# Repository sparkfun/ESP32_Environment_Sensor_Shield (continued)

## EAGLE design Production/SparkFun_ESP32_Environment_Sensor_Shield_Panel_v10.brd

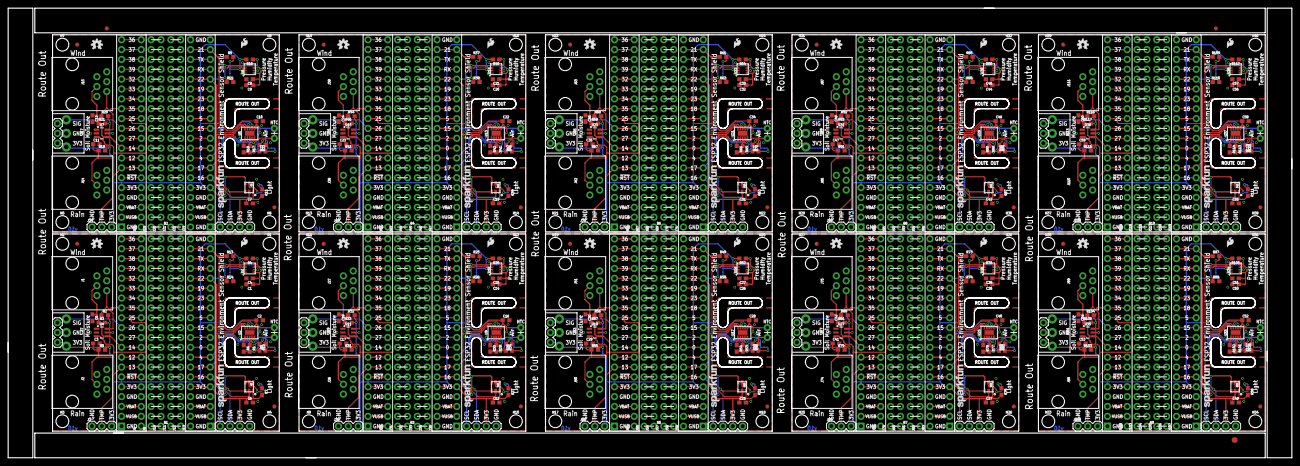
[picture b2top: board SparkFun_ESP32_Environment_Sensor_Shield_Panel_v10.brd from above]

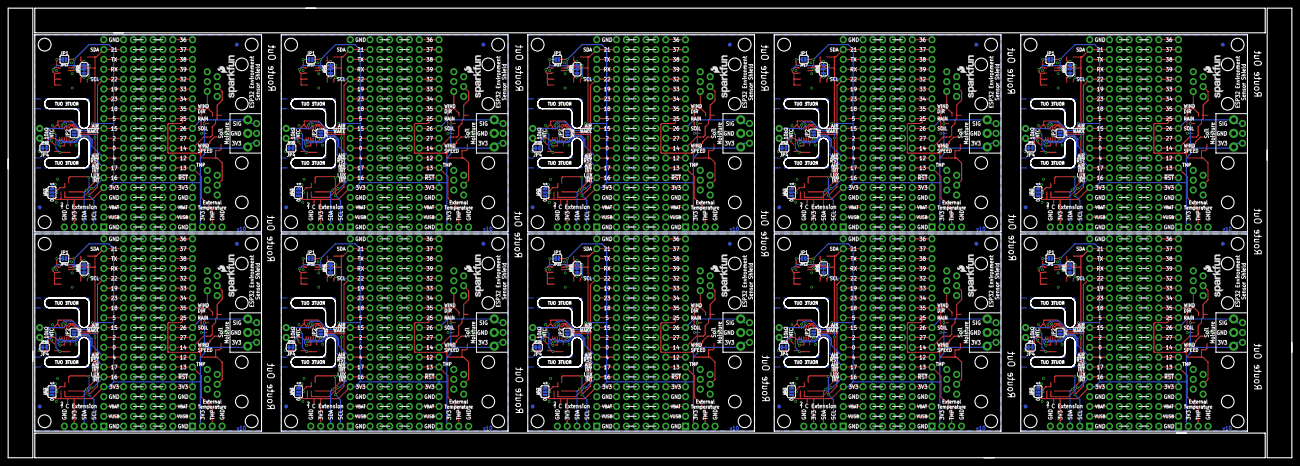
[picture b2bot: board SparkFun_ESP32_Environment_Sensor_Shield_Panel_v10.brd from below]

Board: 2 copper layers, 330.7 x 115.8 mm, 523 parts (80 on the bottom side), 840 nets.

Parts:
B1, B2, B3, B4, B5, B6, B7, B8, B9, B10: ESP32_THING_WO_ANT_KEEPOUT; ESP32_THING_NO_ANT
C1, C4, C6, C7, C8, C9, C13, C14, C15, C19, C20, C21, C25, C26, C27, C31, C32, C33, C37, C38, C39, C43, C44, C45, C49, C50, C51, C55, C56, C57: 0.1uF; 0603
C2, C3, C5, C10, C11, C12, C16, C17, C18, C22, C23, C24, C28, C29, C30, C34, C35, C36, C40, C41, C42, C46, C47, C48, C52, C53, C54, C58, C59, C60: 1.0uF; 0603
E$1: FIDUCIAL-1.5X3
E$7, E$8: FIDUCIAL-1X2
FD1, FD2, FD3, FD4, FD5, FD6, FD7, FD8, FD9, FD10, FD11, FD12, FD13, FD14, FD15, FD16, FD17, FD18, FD19, FD20, FD21, FD22, FD23, FD24, FD25, FD26, FD27, FD28, FD29, FD30, FD31, FD32, FD33, FD34, FD35, FD36, FD37, FD38, FD39, FD40: FIDUCIAL1X2; FIDUCIAL-1X2
H1, H2, H3, H4, H5, H6, H7, H8, H9, H10, H11, H12, H13, H14, H15, H16, H17, H18, H19, H20, H21, H22, H23, H24, H25, H26, H27, H28, H29, H30, H31, H32, H33, H34, H35, H36, H37, H38, H39, H40: STAND-OFF
J1, J15, J27, J39, J51, J63, J75, J87, J99, J111: WEATHER_METER-WIND; RJ11-6
J2, J14, J26, J38, J50, J62, J74, J86, J98, J110: WEATHER_METER-RAIN; RJ11-6
J3, J5, J16, J24, J28, J36, J40, J48, J52, J60, J64, J72, J76, J84, J88, J96, J100, J108, J112, J120: 1X03
J4, J9, J10, J11, J12, J13, J18, J19, J20, J21, J22, J23, J30, J31, J32, J33, J34, J35, J42, J43, J44, J45, J46, J47, J54, J55, J56, J57, J58, J59, J66, J67, J68, J69, J70, J71, J78, J79, J80, J81, J82, J83, J90, J91, J92, J93, J94, J95, J102, J103, J104, J105, J106, J107, J114, J115, J116, J117, J118, J119: 1X20_NOSILK
J6, J8, J25, J37, J49, J61, J73, J85, J97, J109: 1X04
J7, J17, J29, J41, J53, J65, J77, J89, J101, J113: SCREWTERMINAL-3.5MM-3-NS
JP1, JP2, JP7, JP8, JP12, JP13, JP17, JP18, JP22, JP23, JP27, JP28, JP32, JP33, JP37, JP38, JP42, JP43, JP47, JP48: SMT-JUMPER_2_NO_SILK
JP3, JP6, JP11, JP16, JP21, JP26, JP31, JP36, JP41, JP46: SMT-JUMPER_3_NO_SILK
JP4, JP9, JP14, JP19, JP24, JP29, JP34, JP39, JP44, JP49: SMT-JUMPER_2_NC_TRACE_SILK
JP5, JP10, JP15, JP20, JP25, JP30, JP35, JP40, JP45, JP50: SMT-JUMPER_3_2-NC_TRACE_SILK
LOGO1, LOGO5, LOGO9, LOGO13, LOGO17, LOGO21, LOGO25, LOGO29, LOGO33, LOGO37: SFE_LOGO_NAME.1_INCH; SFE_LOGO_NAME_.1
LOGO2, LOGO7, LOGO11, LOGO15, LOGO19, LOGO23, LOGO27, LOGO31, LOGO35, LOGO39: SFE_LOGO_NAME_FLAME.1_INCH; SFE_LOGO_NAME_FLAME_.1
LOGO3, LOGO8, LOGO12, LOGO16, LOGO20, LOGO24, LOGO28, LOGO32, LOGO36, LOGO40: SFE_LOGO_FLAME.1_INCH; SFE_LOGO_FLAME_.1
LOGO4, LOGO6, LOGO10, LOGO14, LOGO18, LOGO22, LOGO26, LOGO30, LOGO34, LOGO38: OSHW-LOGOS; OSHW-LOGO-S
R1, R4, R6, R7, R15, R16, R17, R18, R27, R28, R29, R30, R39, R40, R41, R42, R51, R52, R53, R54, R63, R64, R65, R66, R75, R76, R77, R78, R87, R88, R89, R90, R99, R100, R101, R102, R111, R112, R113, R114: 100k; 0603
R2, R8, R10, R20, R22, R23, R32, R34, R35, R44, R46, R47, R56, R58, R59, R68, R70, R71, R80, R82, R83, R92, R94, R95, R104, R106, R107, R116, R118, R119: 10k; 0603
R3, R9, R19, R21, R31, R33, R43, R45, R55, R57, R67, R69, R79, R81, R91, R93, R103, R105, R115, R117: 1k; 0603
R5, R11, R13, R14, R25, R26, R37, R38, R49, R50, R61, R62, R73, R74, R85, R86, R97, R98, R109, R110: 4.7k; 0603
R12, R24, R36, R48, R60, R72, R84, R96, R108, R120: DNP; AXIAL-0.1
U1, U6, U10, U14, U18, U22, U26, U30, U34, U38: BME280; LGA-8-2.5X2.5
U2, U5, U9, U13, U17, U21, U25, U29, U33, U37: CCS811; LGA10-2.7X4.0MM
U3, U8, U12, U16, U20, U24, U28, U32, U36, U40: APDS-9301; CHIPLED-6
U4, U7, U11, U15, U19, U23, U27, U31, U35, U39: TVS Diode; SOT-23-6

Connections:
3.3V: B1.5, B1.36, C1.1, C2.1, C4.1, C6.1, J3.3, J4.5, J5.1, J7.3, J8.2, J13.5, JP5.2, R1.2, R2.2, R3.2, R4.2, R6.2, R7.2, R9.2, R10.2, U1.2, U1.6, U1.8, U2.6, U3.P1, U4.5
3.3V1: B2.5, B2.36, C7.1, C8.1, C9.1, C10.1, J6.2, J16.1, J17.3, J18.5, J23.5, J24.3, JP10.2, R15.2, R16.2, R17.2, R18.2, R19.2, R20.2, R21.2, R22.2, U5.6, U6.2, U6.6, U6.8, U7.5, U8.P1
3.3V2: B3.5, B3.36, C13.1, C14.1, C15.1, C16.1, J25.2, J28.1, J29.3, J30.5, J35.5, J36.3, JP15.2, R27.2, R28.2, R29.2, R30.2, R31.2, R32.2, R33.2, R34.2, U9.6, U10.2, U10.6, U10.8, U11.5, U12.P1
3.3V3: B4.5, B4.36, C19.1, C20.1, C21.1, C22.1, J37.2, J40.1, J41.3, J42.5, J47.5, J48.3, JP20.2, R39.2, R40.2, R41.2, R42.2, R43.2, R44.2, R45.2, R46.2, U13.6, U14.2, U14.6, U14.8, U15.5, U16.P1
3.3V4: B5.5, B5.36, C25.1, C26.1, C27.1, C28.1, J49.2, J52.1, J53.3, J54.5, J59.5, J60.3, JP25.2, R51.2, R52.2, R53.2, R54.2, R55.2, R56.2, R57.2, R58.2, U17.6, U18.2, U18.6, U18.8, U19.5, U20.P1
3.3V5: B6.5, B6.36, C31.1, C32.1, C33.1, C34.1, J61.2, J64.1, J65.3, J66.5, J71.5, J72.3, JP30.2, R63.2, R64.2, R65.2, R66.2, R67.2, R68.2, R69.2, R70.2, U21.6, U22.2, U22.6, U22.8, U23.5, U24.P1
3.3V6: B7.5, B7.36, C37.1, C38.1, C39.1, C40.1, J73.2, J76.1, J77.3, J78.5, J83.5, J84.3, JP35.2, R75.2, R76.2, R77.2, R78.2, R79.2, R80.2, R81.2, R82.2, U25.6, U26.2, U26.6, U26.8, U27.5, U28.P1
3.3V7: B8.5, B8.36, C43.1, C44.1, C45.1, C46.1, J85.2, J88.1, J89.3, J90.5, J95.5, J96.3, JP40.2, R87.2, R88.2, R89.2, R90.2, R91.2, R92.2, R93.2, R94.2, U29.6, U30.2, U30.6, U30.8, U31.5, U32.P1
3.3V8: B9.5, B9.36, C49.1, C50.1, C51.1, C52.1, J97.2, J100.1, J101.3, J102.5, J107.5, J108.3, JP45.2, R99.2, R100.2, R101.2, R102.2, R103.2, R104.2, R105.2, R106.2, U33.6, U34.2, U34.6, U34.8, U35.5, U36.P1
3.3V9: B10.5, B10.36, C55.1, C56.1, C57.1, C58.1, J109.2, J112.1, J113.3, J114.5, J119.5, J120.3, JP50.2, R111.2, R112.2, R113.2, R114.2, R115.2, R116.2, R117.2, R118.2, U37.6, U38.2, U38.6, U38.8, U39.5, U40.P1
ADDR_TSL1: JP6.2, U8.P3
ADDR_TSL2: JP11.2, U12.P3
ADDR_TSL3: JP16.2, U16.P3
ADDR_TSL4: JP21.2, U20.P3
ADDR_TSL5: JP26.2, U24.P3
ADDR_TSL6: JP31.2, U28.P3
ADDR_TSL7: JP36.2, U32.P3
ADDR_TSL8: JP41.2, U36.P3
ADDR_TSL9: JP46.2, U40.P3
ADDR_TSL2561: JP3.2, U3.P3
CCS811_!INT!: B1.34, J13.7, U2.3
CCS811_!INT!1: B2.34, J23.7, U5.3
CCS811_!INT!2: B3.34, J35.7, U9.3
CCS811_!INT!3: B4.34, J47.7, U13.3
CCS811_!INT!4: B5.34, J59.7, U17.3
CCS811_!INT!5: B6.34, J71.7, U21.3
CCS811_!INT!6: B7.34, J83.7, U25.3
CCS811_!INT!7: B8.34, J95.7, U29.3
CCS811_!INT!8: B9.34, J107.7, U33.3
CCS811_!INT!9: B10.34, J119.7, U37.3
CCS811_!RST!: B1.33, J13.8, R1.1, U2.2
CCS811_!RST!1: B2.33, J23.8, R17.1, U5.2
CCS811_!RST!2: B3.33, J35.8, R29.1, U9.2
CCS811_!RST!3: B4.33, J47.8, R41.1, U13.2
CCS811_!RST!4: B5.33, J59.8, R53.1, U17.2
CCS811_!RST!5: B6.33, J71.8, R65.1, U21.2
CCS811_!RST!6: B7.33, J83.8, R77.1, U25.2
CCS811_!RST!7: B8.33, J95.8, R89.1, U29.2
CCS811_!RST!8: B9.33, J107.8, R101.1, U33.2
CCS811_!RST!9: B10.33, J119.8, R113.1, U37.2
CCS811_!WAKE!: B1.30, J13.11, U2.7
CCS811_!WAKE!1: B2.30, J23.11, U5.7
CCS811_!WAKE!2: B3.30, J35.11, U9.7
CCS811_!WAKE!3: B4.30, J47.11, U13.7
CCS811_!WAKE!4: B5.30, J59.11, U17.7
CCS811_!WAKE!5: B6.30, J71.11, U21.7
CCS811_!WAKE!6: B7.30, J83.11, U25.7
CCS811_!WAKE!7: B8.30, J95.11, U29.7
CCS811_!WAKE!8: B9.30, J107.11, U33.7
CCS811_!WAKE!9: B10.30, J119.11, U37.7
CCS811_ADDR: JP2.2, R6.1, U2.1
CCS811_ADDR1: JP8.2, R18.1, U5.1
CCS811_ADDR2: JP13.2, R30.1, U9.1
CCS811_ADDR3: JP18.2, R42.1, U13.1
CCS811_ADDR4: JP23.2, R54.1, U17.1
CCS811_ADDR5: JP28.2, R66.1, U21.1
CCS811_ADDR6: JP33.2, R78.1, U25.1
CCS811_ADDR7: JP38.2, R90.1, U29.1
CCS811_ADDR8: JP43.2, R102.1, U33.1
CCS811_ADDR9: JP48.2, R114.1, U37.1
CCS811_AUX: JP4.2, R10.1, R12.P$1, U2.8
CCS811_AUX1: JP9.2, R22.1, R24.P$1, U5.8
CCS811_AUX2: JP14.2, R34.1, R36.P$1, U9.8
CCS811_AUX3: JP19.2, R46.1, R48.P$1, U13.8
CCS811_AUX4: JP24.2, R58.1, R60.P$1, U17.8
CCS811_AUX5: JP29.2, R70.1, R72.P$1, U21.8
CCS811_AUX6: JP34.2, R82.1, R84.P$1, U25.8
CCS811_AUX7: JP39.2, R94.1, R96.P$1, U29.8
CCS811_AUX8: JP44.2, R106.1, R108.P$1, U33.8
CCS811_AUX9: JP49.2, R118.1, R120.P$1, U37.8
EXT_TEMPERATURE: B1.7, J3.2, J4.7
EXT_TEMPERATURE1: B2.7, J18.7, J24.2
EXT_TEMPERATURE2: B3.7, J30.7, J36.2
EXT_TEMPERATURE3: B4.7, J42.7, J48.2
EXT_TEMPERATURE4: B5.7, J54.7, J60.2
EXT_TEMPERATURE5: B6.7, J66.7, J72.2
EXT_TEMPERATURE6: B7.7, J78.7, J84.2
EXT_TEMPERATURE7: B8.7, J90.7, J96.2
EXT_TEMPERATURE8: B9.7, J102.7, J108.2
EXT_TEMPERATURE9: B10.7, J114.7, J120.2
GND: B1.1, B1.4, B1.21, B1.37, B1.40, C1.2, C2.2, C3.2, C4.2, C5.2, C6.2, J1.2, J1.3, J2.3, J3.1, J4.1, J4.4, J5.2, J7.2, J8.1, J13.1, J13.4, J13.20, JP1.1, JP2.1, JP3.1, U1.1, U1.7, U2.EP, U3.P2, U4.2
GND1: B2.1, B2.4, B2.21, B2.37, B2.40, C7.2, C8.2, C9.2, C10.2, C11.2, C12.2, J6.1, J14.3, J15.2, J15.3, J16.2, J17.2, J18.1, J18.4, J23.1, J23.4, J23.20, J24.1, JP6.1, JP7.1, JP8.1, U5.EP, U6.1, U6.7, U7.2, U8.P2
GND2: B3.1, B3.4, B3.21, B3.37, B3.40, C13.2, C14.2, C15.2, C16.2, C17.2, C18.2, J25.1, J26.3, J27.2, J27.3, J28.2, J29.2, J30.1, J30.4, J35.1, J35.4, J35.20, J36.1, JP11.1, JP12.1, JP13.1, U9.EP, U10.1, U10.7, U11.2, U12.P2
GND3: B4.1, B4.4, B4.21, B4.37, B4.40, C19.2, C20.2, C21.2, C22.2, C23.2, C24.2, J37.1, J38.3, J39.2, J39.3, J40.2, J41.2, J42.1, J42.4, J47.1, J47.4, J47.20, J48.1, JP16.1, JP17.1, JP18.1, U13.EP, U14.1, U14.7, U15.2, U16.P2
GND4: B5.1, B5.4, B5.21, B5.37, B5.40, C25.2, C26.2, C27.2, C28.2, C29.2, C30.2, J49.1, J50.3, J51.2, J51.3, J52.2, J53.2, J54.1, J54.4, J59.1, J59.4, J59.20, J60.1, JP21.1, JP22.1, JP23.1, U17.EP, U18.1, U18.7, U19.2, U20.P2
GND5: B6.1, B6.4, B6.21, B6.37, B6.40, C31.2, C32.2, C33.2, C34.2, C35.2, C36.2, J61.1, J62.3, J63.2, J63.3, J64.2, J65.2, J66.1, J66.4, J71.1, J71.4, J71.20, J72.1, JP26.1, JP27.1, JP28.1, U21.EP, U22.1, U22.7, U23.2, U24.P2
GND6: B7.1, B7.4, B7.21, B7.37, B7.40, C37.2, C38.2, C39.2, C40.2, C41.2, C42.2, J73.1, J74.3, J75.2, J75.3, J76.2, J77.2, J78.1, J78.4, J83.1, J83.4, J83.20, J84.1, JP31.1, JP32.1, JP33.1, U25.EP, U26.1, U26.7, U27.2, U28.P2
GND7: B8.1, B8.4, B8.21, B8.37, B8.40, C43.2, C44.2, C45.2, C46.2, C47.2, C48.2, J85.1, J86.3, J87.2, J87.3, J88.2, J89.2, J90.1, J90.4, J95.1, J95.4, J95.20, J96.1, JP36.1, JP37.1, JP38.1, U29.EP, U30.1, U30.7, U31.2, U32.P2
GND8: B9.1, B9.4, B9.21, B9.37, B9.40, C49.2, C50.2, C51.2, C52.2, C53.2, C54.2, J97.1, J98.3, J99.2, J99.3, J100.2, J101.2, J102.1, J102.4, J107.1, J107.4, J107.20, J108.1, JP41.1, JP42.1, JP43.1, U33.EP, U34.1, U34.7, U35.2, U36.P2
GND9: B10.1, B10.4, B10.21, B10.37, B10.40, C55.2, C56.2, C57.2, C58.2, C59.2, C60.2, J109.1, J110.3, J111.2, J111.3, J112.2, J113.2, J114.1, J114.4, J119.1, J119.4, J119.20, J120.1, JP46.1, JP47.1, JP48.1, U37.EP, U38.1, U38.7, U39.2, U40.P2
LUX_INT: B1.35, J13.6, U3.P6
LUX_INT1: B2.35, J23.6, U8.P6
LUX_INT2: B3.35, J35.6, U12.P6
LUX_INT3: B4.35, J47.6, U16.P6
LUX_INT4: B5.35, J59.6, U20.P6
LUX_INT5: B6.35, J71.6, U24.P6
LUX_INT6: B7.35, J83.6, U28.P6
LUX_INT7: B8.35, J95.6, U32.P6
LUX_INT8: B9.35, J107.6, U36.P6
LUX_INT9: B10.35, J119.6, U40.P6
unnamed: JP3.3, R7.1
unnamed: JP1.2, R4.1, U1.5
unnamed: JP4.1, R8.1
unnamed: JP5.3, R13.2
unnamed: JP5.1, R14.2
unnamed: B1.2, J4.2
unnamed: B1.3, J4.3
unnamed: B1.6, J4.6
unnamed: B1.10, J4.10
unnamed: JP6.3, R15.1
unnamed: B1.14, J4.14
unnamed: B1.15, J4.15
unnamed: B1.16, J4.16
unnamed: B1.17, J4.17
unnamed: B1.18, J4.18
unnamed: B1.19, J4.19
unnamed: B1.20, J4.20
unnamed: B1.39, J13.2
unnamed: B1.38, J13.3
unnamed: B1.32, J13.9
unnamed: B1.31, J13.10
unnamed: B1.8, J4.8
unnamed: B1.29, J13.12
unnamed: B1.28, J13.13
unnamed: B1.27, J13.14
unnamed: B1.26, J13.15
unnamed: B1.24, J13.17
unnamed: B1.23, J13.18
unnamed: J11.1, J12.1
unnamed: J11.2, J12.2
unnamed: J11.3, J12.3
unnamed: J11.4, J12.4
unnamed: J11.5, J12.5
unnamed: J11.6, J12.6
unnamed: J11.7, J12.7
unnamed: J11.8, J12.8
unnamed: J11.9, J12.9
unnamed: J11.10, J12.10
unnamed: J11.11, J12.11
unnamed: J11.12, J12.12
unnamed: J11.13, J12.13
unnamed: J11.14, J12.14
unnamed: J11.15, J12.15
unnamed: J11.16, J12.16
unnamed: J11.17, J12.17
unnamed: J11.18, J12.18
unnamed: J11.19, J12.19
unnamed: J11.20, J12.20
unnamed: J9.1, J10.1
unnamed: J9.2, J10.2
unnamed: J9.3, J10.3
unnamed: J9.4, J10.4
unnamed: J9.5, J10.5
unnamed: J9.6, J10.6
unnamed: J9.7, J10.7
unnamed: J9.8, J10.8
unnamed: J9.9, J10.9
unnamed: J9.10, J10.10
unnamed: J9.11, J10.11
unnamed: J9.12, J10.12
unnamed: J9.13, J10.13
unnamed: J9.14, J10.14
unnamed: J9.15, J10.15
unnamed: J9.16, J10.16
unnamed: J9.17, J10.17
unnamed: J9.18, J10.18
unnamed: J9.19, J10.19
unnamed: J9.20, J10.20
unnamed: JP7.2, R16.1, U6.5
unnamed: JP9.1, R23.1
unnamed: JP10.3, R5.2
unnamed: JP10.1, R11.2
unnamed: B2.2, J18.2
unnamed: B2.3, J18.3
unnamed: B2.6, J18.6
unnamed: B2.14, J18.14
unnamed: B2.15, J18.15
unnamed: B2.16, J18.16
unnamed: B2.17, J18.17
unnamed: B2.18, J18.18
unnamed: B2.19, J18.19
unnamed: B2.20, J18.20
unnamed: B2.39, J23.2
unnamed: B2.38, J23.3
unnamed: B2.32, J23.9
unnamed: B2.29, J23.12
unnamed: B2.28, J23.13
unnamed: B2.27, J23.14
unnamed: B2.26, J23.15
unnamed: B2.24, J23.17
unnamed: B2.23, J23.18
unnamed: J21.1, J22.1
unnamed: J21.2, J22.2
unnamed: J21.3, J22.3
unnamed: J21.4, J22.4
unnamed: J21.5, J22.5
unnamed: J21.6, J22.6
unnamed: J21.7, J22.7
unnamed: J21.8, J22.8
unnamed: J21.9, J22.9
unnamed: J21.10, J22.10
unnamed: J21.11, J22.11
unnamed: J21.12, J22.12
unnamed: J21.13, J22.13
unnamed: J21.14, J22.14
unnamed: J21.15, J22.15
unnamed: J21.16, J22.16
unnamed: J21.17, J22.17
unnamed: J21.18, J22.18
unnamed: J21.19, J22.19
unnamed: J21.20, J22.20
unnamed: J19.1, J20.1
unnamed: J19.2, J20.2
unnamed: J19.3, J20.3
unnamed: J19.4, J20.4
unnamed: J19.5, J20.5
unnamed: J19.6, J20.6
unnamed: J19.7, J20.7
unnamed: J19.8, J20.8
unnamed: J19.9, J20.9
unnamed: J19.10, J20.10
unnamed: J19.11, J20.11
unnamed: J19.12, J20.12
unnamed: J19.13, J20.13
unnamed: J19.14, J20.14
unnamed: J19.15, J20.15
unnamed: J19.16, J20.16
unnamed: J19.17, J20.17
unnamed: J19.18, J20.18
unnamed: J19.19, J20.19
unnamed: J19.20, J20.20
unnamed: B2.31, J23.10
unnamed: B2.8, J18.8
unnamed: B2.10, J18.10
unnamed: JP11.3, R27.1
unnamed: JP12.2, R28.1, U10.5
unnamed: JP14.1, R35.1
unnamed: JP15.3, R25.2
unnamed: JP15.1, R26.2
unnamed: B3.2, J30.2
unnamed: B3.3, J30.3
unnamed: B3.6, J30.6
unnamed: B3.14, J30.14
unnamed: B3.15, J30.15
unnamed: B3.16, J30.16
unnamed: B3.17, J30.17
unnamed: B3.18, J30.18
unnamed: B3.19, J30.19
unnamed: B3.20, J30.20
unnamed: B3.39, J35.2
unnamed: B3.38, J35.3
unnamed: B3.32, J35.9
unnamed: B3.29, J35.12
unnamed: B3.28, J35.13
unnamed: B3.27, J35.14
unnamed: B3.26, J35.15
unnamed: B3.24, J35.17
unnamed: B3.23, J35.18
unnamed: J33.1, J34.1
unnamed: J33.2, J34.2
unnamed: J33.3, J34.3
unnamed: J33.4, J34.4
unnamed: J33.5, J34.5
unnamed: J33.6, J34.6
unnamed: J33.7, J34.7
unnamed: J33.8, J34.8
unnamed: J33.9, J34.9
unnamed: J33.10, J34.10
unnamed: J33.11, J34.11
unnamed: J33.12, J34.12
unnamed: J33.13, J34.13
unnamed: J33.14, J34.14
unnamed: J33.15, J34.15
unnamed: J33.16, J34.16
unnamed: J33.17, J34.17
unnamed: J33.18, J34.18
unnamed: J33.19, J34.19
unnamed: J33.20, J34.20
unnamed: J31.1, J32.1
unnamed: J31.2, J32.2
unnamed: J31.3, J32.3
unnamed: J31.4, J32.4
unnamed: J31.5, J32.5
unnamed: J31.6, J32.6
unnamed: J31.7, J32.7
unnamed: J31.8, J32.8
unnamed: J31.9, J32.9
unnamed: J31.10, J32.10
unnamed: J31.11, J32.11
unnamed: J31.12, J32.12
unnamed: J31.13, J32.13
unnamed: J31.14, J32.14
unnamed: J31.15, J32.15
unnamed: J31.16, J32.16
unnamed: J31.17, J32.17
unnamed: J31.18, J32.18
unnamed: J31.19, J32.19
unnamed: J31.20, J32.20
unnamed: B3.31, J35.10
unnamed: B3.8, J30.8
unnamed: B3.10, J30.10
unnamed: JP16.3, R39.1
unnamed: JP17.2, R40.1, U14.5
unnamed: JP19.1, R47.1
unnamed: JP20.3, R37.2
unnamed: JP20.1, R38.2
unnamed: B4.2, J42.2
unnamed: B4.3, J42.3
unnamed: B4.6, J42.6
unnamed: B4.14, J42.14
unnamed: B4.15, J42.15
unnamed: B4.16, J42.16
unnamed: B4.17, J42.17
unnamed: B4.18, J42.18
unnamed: B4.19, J42.19
unnamed: B4.20, J42.20
unnamed: B4.39, J47.2
unnamed: B4.38, J47.3
unnamed: B4.32, J47.9
unnamed: B4.29, J47.12
unnamed: B4.28, J47.13
unnamed: B4.27, J47.14
unnamed: B4.26, J47.15
unnamed: B4.24, J47.17
unnamed: B4.23, J47.18
unnamed: J45.1, J46.1
unnamed: J45.2, J46.2
unnamed: J45.3, J46.3
unnamed: J45.4, J46.4
unnamed: J45.5, J46.5
unnamed: J45.6, J46.6
unnamed: J45.7, J46.7
unnamed: J45.8, J46.8
unnamed: J45.9, J46.9
unnamed: J45.10, J46.10
unnamed: J45.11, J46.11
unnamed: J45.12, J46.12
unnamed: J45.13, J46.13
unnamed: J45.14, J46.14
unnamed: J45.15, J46.15
unnamed: J45.16, J46.16
unnamed: J45.17, J46.17
unnamed: J45.18, J46.18
unnamed: J45.19, J46.19
unnamed: J45.20, J46.20
unnamed: J43.1, J44.1
unnamed: J43.2, J44.2
unnamed: J43.3, J44.3
unnamed: J43.4, J44.4
unnamed: J43.5, J44.5
unnamed: J43.6, J44.6
unnamed: J43.7, J44.7
unnamed: J43.8, J44.8
unnamed: J43.9, J44.9
unnamed: J43.10, J44.10
unnamed: J43.11, J44.11
unnamed: J43.12, J44.12
unnamed: J43.13, J44.13
unnamed: J43.14, J44.14
unnamed: J43.15, J44.15
unnamed: J43.16, J44.16
unnamed: J43.17, J44.17
unnamed: J43.18, J44.18
unnamed: J43.19, J44.19
unnamed: J43.20, J44.20
unnamed: B4.31, J47.10
unnamed: B4.8, J42.8
unnamed: B4.10, J42.10
unnamed: JP21.3, R51.1
unnamed: JP22.2, R52.1, U18.5
unnamed: JP24.1, R59.1
unnamed: JP25.3, R49.2
unnamed: JP25.1, R50.2
unnamed: B5.2, J54.2
unnamed: B5.3, J54.3
unnamed: B5.6, J54.6
unnamed: B5.14, J54.14
unnamed: B5.15, J54.15
unnamed: B5.16, J54.16
unnamed: B5.17, J54.17
unnamed: B5.18, J54.18
unnamed: B5.19, J54.19
unnamed: B5.20, J54.20
unnamed: B5.39, J59.2
unnamed: B5.38, J59.3
unnamed: B5.32, J59.9
unnamed: B5.29, J59.12
unnamed: B5.28, J59.13
unnamed: B5.27, J59.14
unnamed: B5.26, J59.15
unnamed: B5.24, J59.17
unnamed: B5.23, J59.18
unnamed: J57.1, J58.1
unnamed: J57.2, J58.2
unnamed: J57.3, J58.3
unnamed: J57.4, J58.4
unnamed: J57.5, J58.5
unnamed: J57.6, J58.6
unnamed: J57.7, J58.7
unnamed: J57.8, J58.8
unnamed: J57.9, J58.9
unnamed: J57.10, J58.10
unnamed: J57.11, J58.11
unnamed: J57.12, J58.12
unnamed: J57.13, J58.13
unnamed: J57.14, J58.14
unnamed: J57.15, J58.15
unnamed: J57.16, J58.16
unnamed: J57.17, J58.17
unnamed: J57.18, J58.18
unnamed: J57.19, J58.19
unnamed: J57.20, J58.20
unnamed: J55.1, J56.1
unnamed: J55.2, J56.2
unnamed: J55.3, J56.3
unnamed: J55.4, J56.4
unnamed: J55.5, J56.5
unnamed: J55.6, J56.6
unnamed: J55.7, J56.7
unnamed: J55.8, J56.8
unnamed: J55.9, J56.9
unnamed: J55.10, J56.10
unnamed: J55.11, J56.11
unnamed: J55.12, J56.12
unnamed: J55.13, J56.13
unnamed: J55.14, J56.14
unnamed: J55.15, J56.15
unnamed: J55.16, J56.16
unnamed: J55.17, J56.17
unnamed: J55.18, J56.18
unnamed: J55.19, J56.19
unnamed: J55.20, J56.20
unnamed: B5.31, J59.10
unnamed: B5.8, J54.8
unnamed: B5.10, J54.10
unnamed: JP26.3, R63.1
unnamed: JP27.2, R64.1, U22.5
unnamed: JP29.1, R71.1
unnamed: JP30.3, R61.2
unnamed: JP30.1, R62.2
unnamed: B6.2, J66.2
unnamed: B6.3, J66.3
unnamed: B6.6, J66.6
unnamed: B6.14, J66.14
unnamed: B6.15, J66.15
unnamed: B6.16, J66.16
unnamed: B6.17, J66.17
unnamed: B6.18, J66.18
unnamed: B6.19, J66.19
unnamed: B6.20, J66.20
unnamed: B6.39, J71.2
unnamed: B6.38, J71.3
unnamed: B6.32, J71.9
unnamed: B6.29, J71.12
unnamed: B6.28, J71.13
unnamed: B6.27, J71.14
unnamed: B6.26, J71.15
unnamed: B6.24, J71.17
unnamed: B6.23, J71.18
unnamed: J69.1, J70.1
unnamed: J69.2, J70.2
unnamed: J69.3, J70.3
unnamed: J69.4, J70.4
unnamed: J69.5, J70.5
unnamed: J69.6, J70.6
unnamed: J69.7, J70.7
unnamed: J69.8, J70.8
unnamed: J69.9, J70.9
unnamed: J69.10, J70.10
unnamed: J69.11, J70.11
unnamed: J69.12, J70.12
unnamed: J69.13, J70.13
unnamed: J69.14, J70.14
unnamed: J69.15, J70.15
unnamed: J69.16, J70.16
unnamed: J69.17, J70.17
unnamed: J69.18, J70.18
unnamed: J69.19, J70.19
unnamed: J69.20, J70.20
unnamed: J67.1, J68.1
unnamed: J67.2, J68.2
unnamed: J67.3, J68.3
unnamed: J67.4, J68.4
unnamed: J67.5, J68.5
unnamed: J67.6, J68.6
unnamed: J67.7, J68.7
unnamed: J67.8, J68.8
unnamed: J67.9, J68.9
unnamed: J67.10, J68.10
unnamed: J67.11, J68.11
unnamed: J67.12, J68.12
unnamed: J67.13, J68.13
unnamed: J67.14, J68.14
unnamed: J67.15, J68.15
unnamed: J67.16, J68.16
unnamed: J67.17, J68.17
unnamed: J67.18, J68.18
unnamed: J67.19, J68.19
unnamed: J67.20, J68.20
unnamed: B6.31, J71.10
unnamed: B6.8, J66.8
unnamed: B6.10, J66.10
unnamed: JP31.3, R75.1
unnamed: JP32.2, R76.1, U26.5
unnamed: JP34.1, R83.1
unnamed: JP35.3, R73.2
unnamed: JP35.1, R74.2
unnamed: B7.2, J78.2
unnamed: B7.3, J78.3
unnamed: B7.6, J78.6
unnamed: B7.14, J78.14
unnamed: B7.15, J78.15
unnamed: B7.16, J78.16
unnamed: B7.17, J78.17
unnamed: B7.18, J78.18
unnamed: B7.19, J78.19
unnamed: B7.20, J78.20
unnamed: B7.39, J83.2
unnamed: B7.38, J83.3
unnamed: B7.32, J83.9
unnamed: B7.29, J83.12
unnamed: B7.28, J83.13
unnamed: B7.27, J83.14
unnamed: B7.26, J83.15
unnamed: B7.24, J83.17
unnamed: B7.23, J83.18
unnamed: J81.1, J82.1
unnamed: J81.2, J82.2
unnamed: J81.3, J82.3
unnamed: J81.4, J82.4
unnamed: J81.5, J82.5
unnamed: J81.6, J82.6
unnamed: J81.7, J82.7
unnamed: J81.8, J82.8
unnamed: J81.9, J82.9
unnamed: J81.10, J82.10
unnamed: J81.11, J82.11
unnamed: J81.12, J82.12
unnamed: J81.13, J82.13
unnamed: J81.14, J82.14
unnamed: J81.15, J82.15
unnamed: J81.16, J82.16
unnamed: J81.17, J82.17
unnamed: J81.18, J82.18
unnamed: J81.19, J82.19
unnamed: J81.20, J82.20
unnamed: J79.1, J80.1
unnamed: J79.2, J80.2
unnamed: J79.3, J80.3
unnamed: J79.4, J80.4
unnamed: J79.5, J80.5
unnamed: J79.6, J80.6
unnamed: J79.7, J80.7
unnamed: J79.8, J80.8
unnamed: J79.9, J80.9
unnamed: J79.10, J80.10
unnamed: J79.11, J80.11
unnamed: J79.12, J80.12
unnamed: J79.13, J80.13
unnamed: J79.14, J80.14
unnamed: J79.15, J80.15
unnamed: J79.16, J80.16
unnamed: J79.17, J80.17
unnamed: J79.18, J80.18
unnamed: J79.19, J80.19
unnamed: J79.20, J80.20
unnamed: B7.31, J83.10
unnamed: B7.8, J78.8
unnamed: B7.10, J78.10
unnamed: JP36.3, R87.1
unnamed: JP37.2, R88.1, U30.5
unnamed: JP39.1, R95.1
unnamed: JP40.3, R85.2
unnamed: JP40.1, R86.2
unnamed: B8.2, J90.2
unnamed: B8.3, J90.3
unnamed: B8.6, J90.6
unnamed: B8.14, J90.14
unnamed: B8.15, J90.15
unnamed: B8.16, J90.16
unnamed: B8.17, J90.17
unnamed: B8.18, J90.18
unnamed: B8.19, J90.19
unnamed: B8.20, J90.20
unnamed: B8.39, J95.2
unnamed: B8.38, J95.3
unnamed: B8.32, J95.9
unnamed: B8.29, J95.12
unnamed: B8.28, J95.13
unnamed: B8.27, J95.14
unnamed: B8.26, J95.15
unnamed: B8.24, J95.17
unnamed: B8.23, J95.18
unnamed: J93.1, J94.1
unnamed: J93.2, J94.2
unnamed: J93.3, J94.3
unnamed: J93.4, J94.4
unnamed: J93.5, J94.5
unnamed: J93.6, J94.6
unnamed: J93.7, J94.7
unnamed: J93.8, J94.8
unnamed: J93.9, J94.9
unnamed: J93.10, J94.10
unnamed: J93.11, J94.11
unnamed: J93.12, J94.12
unnamed: J93.13, J94.13
unnamed: J93.14, J94.14
unnamed: J93.15, J94.15
unnamed: J93.16, J94.16
unnamed: J93.17, J94.17
unnamed: J93.18, J94.18
unnamed: J93.19, J94.19
unnamed: J93.20, J94.20
unnamed: J91.1, J92.1
unnamed: J91.2, J92.2
unnamed: J91.3, J92.3
unnamed: J91.4, J92.4
unnamed: J91.5, J92.5
unnamed: J91.6, J92.6
unnamed: J91.7, J92.7
unnamed: J91.8, J92.8
unnamed: J91.9, J92.9
unnamed: J91.10, J92.10
unnamed: J91.11, J92.11
unnamed: J91.12, J92.12
unnamed: J91.13, J92.13
unnamed: J91.14, J92.14
unnamed: J91.15, J92.15
unnamed: J91.16, J92.16
unnamed: J91.17, J92.17
unnamed: J91.18, J92.18
unnamed: J91.19, J92.19
unnamed: J91.20, J92.20
unnamed: B8.31, J95.10
unnamed: B8.8, J90.8
unnamed: B8.10, J90.10
unnamed: JP41.3, R99.1
unnamed: JP42.2, R100.1, U34.5
unnamed: JP44.1, R107.1
unnamed: JP45.3, R97.2
unnamed: JP45.1, R98.2
unnamed: B9.2, J102.2
unnamed: B9.3, J102.3
unnamed: B9.6, J102.6
unnamed: B9.14, J102.14
unnamed: B9.15, J102.15
unnamed: B9.16, J102.16
unnamed: B9.17, J102.17
unnamed: B9.18, J102.18
unnamed: B9.19, J102.19
unnamed: B9.20, J102.20
unnamed: B9.39, J107.2
unnamed: B9.38, J107.3
unnamed: B9.32, J107.9
unnamed: B9.29, J107.12
unnamed: B9.28, J107.13
unnamed: B9.27, J107.14
unnamed: B9.26, J107.15
unnamed: B9.24, J107.17
unnamed: B9.23, J107.18
unnamed: J105.1, J106.1
unnamed: J105.2, J106.2
unnamed: J105.3, J106.3
unnamed: J105.4, J106.4
unnamed: J105.5, J106.5
unnamed: J105.6, J106.6
unnamed: J105.7, J106.7
unnamed: J105.8, J106.8
unnamed: J105.9, J106.9
unnamed: J105.10, J106.10
unnamed: J105.11, J106.11
unnamed: J105.12, J106.12
unnamed: J105.13, J106.13
unnamed: J105.14, J106.14
unnamed: J105.15, J106.15
unnamed: J105.16, J106.16
unnamed: J105.17, J106.17
unnamed: J105.18, J106.18
unnamed: J105.19, J106.19
unnamed: J105.20, J106.20
unnamed: J103.1, J104.1
unnamed: J103.2, J104.2
unnamed: J103.3, J104.3
unnamed: J103.4, J104.4
unnamed: J103.5, J104.5
unnamed: J103.6, J104.6
unnamed: J103.7, J104.7
unnamed: J103.8, J104.8
unnamed: J103.9, J104.9
unnamed: J103.10, J104.10
unnamed: J103.11, J104.11
unnamed: J103.12, J104.12
unnamed: J103.13, J104.13
unnamed: J103.14, J104.14
unnamed: J103.15, J104.15
unnamed: J103.16, J104.16
unnamed: J103.17, J104.17
unnamed: J103.18, J104.18
unnamed: J103.19, J104.19
unnamed: J103.20, J104.20
unnamed: B9.31, J107.10
unnamed: B9.8, J102.8
unnamed: B9.10, J102.10
unnamed: JP46.3, R111.1
unnamed: JP47.2, R112.1, U38.5
unnamed: JP49.1, R119.1
unnamed: JP50.3, R109.2
unnamed: JP50.1, R110.2
unnamed: B10.2, J114.2
unnamed: B10.3, J114.3
unnamed: B10.6, J114.6
unnamed: B10.14, J114.14
unnamed: B10.15, J114.15
unnamed: B10.16, J114.16
unnamed: B10.17, J114.17
unnamed: B10.18, J114.18
unnamed: B10.19, J114.19
unnamed: B10.20, J114.20
unnamed: B10.39, J119.2
unnamed: B10.38, J119.3
unnamed: B10.32, J119.9
unnamed: B10.29, J119.12
unnamed: B10.28, J119.13
unnamed: B10.27, J119.14
unnamed: B10.26, J119.15
unnamed: B10.24, J119.17
unnamed: B10.23, J119.18
unnamed: J117.1, J118.1
unnamed: J117.2, J118.2
unnamed: J117.3, J118.3
unnamed: J117.4, J118.4
unnamed: J117.5, J118.5
unnamed: J117.6, J118.6
unnamed: J117.7, J118.7
unnamed: J117.8, J118.8
unnamed: J117.9, J118.9
unnamed: J117.10, J118.10
unnamed: J117.11, J118.11
unnamed: J117.12, J118.12
unnamed: J117.13, J118.13
unnamed: J117.14, J118.14
unnamed: J117.15, J118.15
unnamed: J117.16, J118.16
unnamed: J117.17, J118.17
unnamed: J117.18, J118.18
unnamed: J117.19, J118.19
unnamed: J117.20, J118.20
unnamed: J115.1, J116.1
unnamed: J115.2, J116.2
unnamed: J115.3, J116.3
unnamed: J115.4, J116.4
unnamed: J115.5, J116.5
unnamed: J115.6, J116.6
unnamed: J115.7, J116.7
unnamed: J115.8, J116.8
unnamed: J115.9, J116.9
unnamed: J115.10, J116.10
unnamed: J115.11, J116.11
unnamed: J115.12, J116.12
unnamed: J115.13, J116.13
unnamed: J115.14, J116.14
unnamed: J115.15, J116.15
unnamed: J115.16, J116.16
unnamed: J115.17, J116.17
unnamed: J115.18, J116.18
unnamed: J115.19, J116.19
unnamed: J115.20, J116.20
unnamed: B10.31, J119.10
unnamed: B10.8, J114.8
unnamed: B10.10, J114.10
NTC_SENSE: R8.2, R12.P$2, U2.4, U2.5
NTC_SENSE1: R23.2, R24.P$2, U5.4, U5.5
NTC_SENSE2: R35.2, R36.P$2, U9.4, U9.5
NTC_SENSE3: R47.2, R48.P$2, U13.4, U13.5
NTC_SENSE4: R59.2, R60.P$2, U17.4, U17.5
NTC_SENSE5: R71.2, R72.P$2, U21.4, U21.5
NTC_SENSE6: R83.2, R84.P$2, U25.4, U25.5
NTC_SENSE7: R95.2, R96.P$2, U29.4, U29.5
NTC_SENSE8: R107.2, R108.P$2, U33.4, U33.5
NTC_SENSE9: R119.2, R120.P$2, U37.4, U37.5
RAINFALL: B1.12, C3.1, J2.4, J4.12, R9.1, U4.3
RAINFALL1: B2.12, C11.1, J14.4, J18.12, R19.1, U7.3
RAINFALL2: B3.12, C17.1, J26.4, J30.12, R31.1, U11.3
RAINFALL3: B4.12, C23.1, J38.4, J42.12, R43.1, U15.3
RAINFALL4: B5.12, C29.1, J50.4, J54.12, R55.1, U19.3
RAINFALL5: B6.12, C35.1, J62.4, J66.12, R67.1, U23.3
RAINFALL6: B7.12, C41.1, J74.4, J78.12, R79.1, U27.3
RAINFALL7: B8.12, C47.1, J86.4, J90.12, R91.1, U31.3
RAINFALL8: B9.12, C53.1, J98.4, J102.12, R103.1, U35.3
RAINFALL9: B10.12, C59.1, J110.4, J114.12, R115.1, U39.3
SCL: B1.25, J8.4, J13.16, R14.1, U1.4, U2.10, U3.P4
SCL1: B2.25, J6.4, J23.16, R11.1, U5.10, U6.4, U8.P4
SCL2: B3.25, J25.4, J35.16, R26.1, U9.10, U10.4, U12.P4
SCL3: B4.25, J37.4, J47.16, R38.1, U13.10, U14.4, U16.P4
SCL4: B5.25, J49.4, J59.16, R50.1, U17.10, U18.4, U20.P4
SCL5: B6.25, J61.4, J71.16, R62.1, U21.10, U22.4, U24.P4
SCL6: B7.25, J73.4, J83.16, R74.1, U25.10, U26.4, U28.P4
SCL7: B8.25, J85.4, J95.16, R86.1, U29.10, U30.4, U32.P4
SCL8: B9.25, J97.4, J107.16, R98.1, U33.10, U34.4, U36.P4
SCL9: B10.25, J109.4, J119.16, R110.1, U37.10, U38.4, U40.P4
SDA: B1.22, J8.3, J13.19, R13.1, U1.3, U2.9, U3.P5
SDA1: B2.22, J6.3, J23.19, R5.1, U5.9, U6.3, U8.P5
SDA2: B3.22, J25.3, J35.19, R25.1, U9.9, U10.3, U12.P5
SDA3: B4.22, J37.3, J47.19, R37.1, U13.9, U14.3, U16.P5
SDA4: B5.22, J49.3, J59.19, R49.1, U17.9, U18.3, U20.P5
SDA5: B6.22, J61.3, J71.19, R61.1, U21.9, U22.3, U24.P5
SDA6: B7.22, J73.3, J83.19, R73.1, U25.9, U26.3, U28.P5
SDA7: B8.22, J85.3, J95.19, R85.1, U29.9, U30.3, U32.P5
SDA8: B9.22, J97.3, J107.19, R97.1, U33.9, U34.3, U36.P5
SDA9: B10.22, J109.3, J119.19, R109.1, U37.9, U38.3, U40.P5
SOIL_MOISTURE: B1.11, J4.11, J5.3, J7.1
SOIL_MOISTURE1: B2.11, J16.3, J17.1, J18.11
SOIL_MOISTURE2: B3.11, J28.3, J29.1, J30.11
SOIL_MOISTURE3: B4.11, J40.3, J41.1, J42.11
SOIL_MOISTURE4: B5.11, J52.3, J53.1, J54.11
SOIL_MOISTURE5: B6.11, J64.3, J65.1, J66.11
SOIL_MOISTURE6: B7.11, J76.3, J77.1, J78.11
SOIL_MOISTURE7: B8.11, J88.3, J89.1, J90.11
SOIL_MOISTURE8: B9.11, J100.3, J101.1, J102.11
SOIL_MOISTURE9: B10.11, J112.3, J113.1, J114.11
WIND_DIR: B1.13, J1.5, J4.13, R2.1, U4.6
WIND_DIR1: B2.13, J15.5, J18.13, R20.1, U7.6
WIND_DIR2: B3.13, J27.5, J30.13, R32.1, U11.6
WIND_DIR3: B4.13, J39.5, J42.13, R44.1, U15.6
WIND_DIR4: B5.13, J51.5, J54.13, R56.1, U19.6
WIND_DIR5: B6.13, J63.5, J66.13, R68.1, U23.6
WIND_DIR6: B7.13, J75.5, J78.13, R80.1, U27.6
WIND_DIR7: B8.13, J87.5, J90.13, R92.1, U31.6
WIND_DIR8: B9.13, J99.5, J102.13, R104.1, U35.6
WIND_DIR9: B10.13, J111.5, J114.13, R116.1, U39.6
WIND_SPEED: B1.9, C5.1, J1.4, J4.9, R3.1, U4.4
WIND_SPEED1: B2.9, C12.1, J15.4, J18.9, R21.1, U7.4
WIND_SPEED2: B3.9, C18.1, J27.4, J30.9, R33.1, U11.4
WIND_SPEED3: B4.9, C24.1, J39.4, J42.9, R45.1, U15.4
WIND_SPEED4: B5.9, C30.1, J51.4, J54.9, R57.1, U19.4
WIND_SPEED5: B6.9, C36.1, J63.4, J66.9, R69.1, U23.4
WIND_SPEED6: B7.9, C42.1, J75.4, J78.9, R81.1, U27.4
WIND_SPEED7: B8.9, C48.1, J87.4, J90.9, R93.1, U31.4
WIND_SPEED8: B9.9, C54.1, J99.4, J102.9, R105.1, U35.4
WIND_SPEED9: B10.9, C60.1, J111.4, J114.9, R117.1, U39.4

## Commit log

2017-01-23 Initial commit of hardware.
2017-01-23 Schematic cleanup. Bussing inner prototyping pins together.
2017-01-23 Adding CCS811 programming guide, NTC guide.
2017-01-23 Connecting CCS811 RST pin to ESP32.
2017-01-23 Labeling in-use pins on bottom side.
2017-01-23 Tweaking CCS811 route out.
2017-01-24 Revising weather meter circuits after tests with ESP32 Thing.
2017-01-25 Adding TVS diode to weather meter signals.
2017-01-25 Post-review fixes: CCS811 paste, spell check
    - Reduced size of CCS811's exposed pad paste aperature
    - Fixed anemometer spelling
    - Changed "Gas" to "Air" labels
    - Clean up schematic
2017-01-26 Minor adjustments after running Engineer checklist.
2017-01-26 Adjustin silkscreen, adding measures to RJ11 jacks, screw terminals.
2017-03-21 Replaced TLS2561 sensor with APDS-9301
2017-03-22 Feedback from review
2017-03-28 Chg rev to 02
2017-03-29 Fix issues from review
2017-04-18 Changes after review of 02 - Change i2c addr info for apds-9301 - Change pin rain sensor is attached to - Add debounce caps to rain sensor and anemometer - Fix APDS-9301 footprint
2017-04-19 Minor cosmetic changes from review
2017-05-02 Add firmware example
2017-05-02 Add APDS-9301 datasheet
2017-05-23 Changes from review
2017-05-30 created panel v10
2017-05-31 removing bad panel
2017-05-31 Removed restrict layers on antenna for panelization
2017-05-31 re-created panel v10
2017-07-07 Ready for release
2017-07-07 Replace APDS datasheet with correct file
2019-05-31 Add Updated CCS811 Datasheet
